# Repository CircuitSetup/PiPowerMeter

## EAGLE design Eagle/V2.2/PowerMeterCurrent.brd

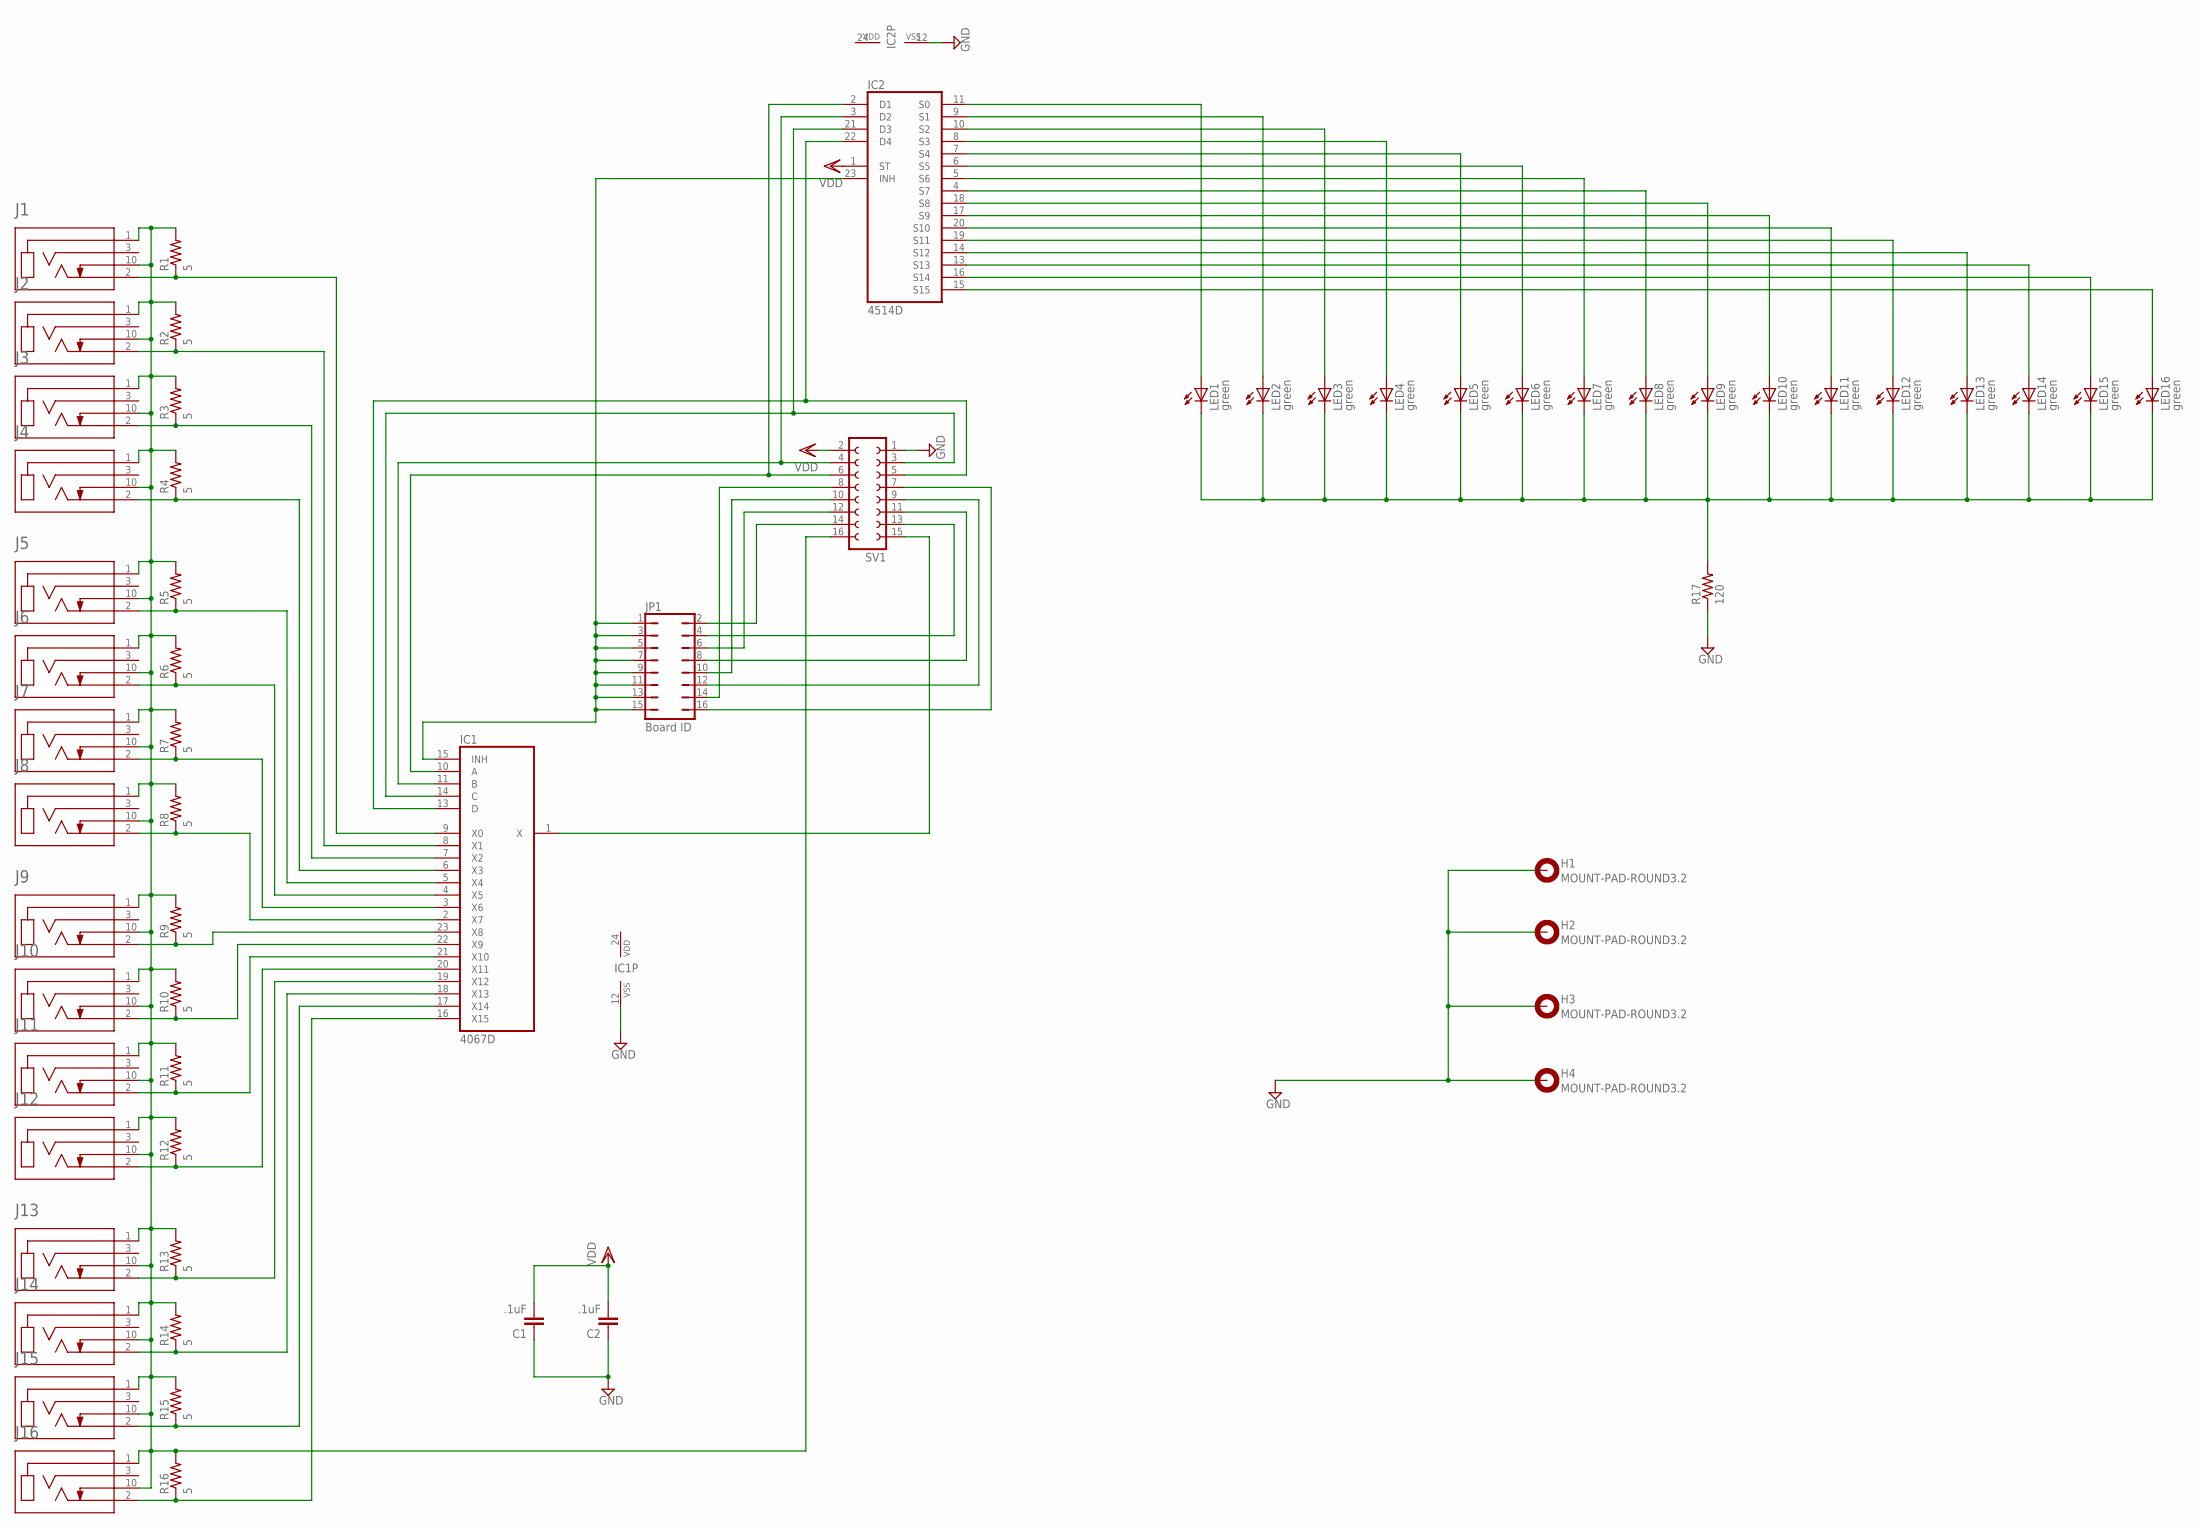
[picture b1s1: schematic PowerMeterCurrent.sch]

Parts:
C1, C2: .1uF; C1206; PARTNO C1206C104K5RAC7867
H1, H2, H3, H4: MOUNT-PAD-ROUND3.2; 3,2-PAD
IC1: 4067D; SO24W; PARTNO 74HC4067D,652
IC2: 4514D; SO24W; PARTNO 74HC4514D,652
J1, J2, J3, J4, J5, J6, J7, J8, J9, J10, J11, J12, J13, J14, J15, J16: SJ2-35813B-SMT-TR; CUI_SJ2-35813B-SMT-TR
JP1: Board ID; JP8Q; PARTNO 67996-416HLF
LED1, LED2, LED3, LED4, LED5, LED6, LED7, LED8, LED9, LED10, LED11, LED12, LED13, LED14, LED15, LED16: green; LED_1206; PARTNO LTST-C150GKT
R1, R2, R3, R4, R5, R6, R7, R8, R9, R10, R11, R12, R13, R14, R15, R16: 5; R1206; PARTNO RC1206FR-075R1L
R17: 120; R1206; PARTNO RC1206FR-07120RL
SV1: FE08-2; PARTNO SSQ-108-02-T-D

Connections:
CT-: J1.1 (SLEEVE), J1.10 (TIP_SWITCH), J2.1 (SLEEVE), J2.10 (TIP_SWITCH), J3.1 (SLEEVE), J3.10 (TIP_SWITCH), J4.1 (SLEEVE), J4.10 (TIP_SWITCH), J5.1 (SLEEVE), J5.10 (TIP_SWITCH), J6.1 (SLEEVE), J6.10 (TIP_SWITCH), J7.1 (SLEEVE), J7.10 (TIP_SWITCH), J8.1 (SLEEVE), J8.10 (TIP_SWITCH), J9.1 (SLEEVE), J9.10 (TIP_SWITCH), J10.1 (SLEEVE), J10.10 (TIP_SWITCH), J11.1 (SLEEVE), J11.10 (TIP_SWITCH), J12.1 (SLEEVE), J12.10 (TIP_SWITCH), J13.1 (SLEEVE), J13.10 (TIP_SWITCH), J14.1 (SLEEVE), J14.10 (TIP_SWITCH), J15.1 (SLEEVE), J15.10 (TIP_SWITCH), J16.1 (SLEEVE), J16.10 (TIP_SWITCH), R1.2, R2.2, R3.2, R4.2, R5.2, R6.2, R7.2, R8.2, R9.2, R10.2, R11.2, R12.2, R13.2, R14.2, R15.2, R16.2, SV1.16
GND: C1.1, C2.1, H1.B3,2, H2.B3,2, H3.B3,2, H4.B3,2, IC1.12 (VSS), IC2.12 (VSS), R17.1, SV1.1
unnamed: IC1.10 (A), IC2.2 (D1), SV1.6
unnamed: IC2.15 (S15), LED16.A
unnamed: IC1.11 (B), IC2.3 (D2), SV1.4
unnamed: IC1.14 (C), IC2.21 (D3), SV1.3
unnamed: IC1.13 (D), IC2.22 (D4), SV1.5
unnamed: IC1.15 (INH), IC2.23 (INH), JP1.1, JP1.3, JP1.5, JP1.7, JP1.9, JP1.11, JP1.13, JP1.15
unnamed: JP1.14, SV1.8
unnamed: JP1.10, SV1.10
unnamed: IC2.16 (S14), LED15.A
unnamed: JP1.6, SV1.12
unnamed: JP1.2, SV1.14
unnamed: JP1.4, SV1.13
unnamed: JP1.8, SV1.11
unnamed: JP1.12, SV1.9
unnamed: JP1.16, SV1.7
unnamed: IC1.1 (X), SV1.15
unnamed: IC1.5 (X4), J5.2 (TIP), R5.1
unnamed: IC2.13 (S13), LED14.A
unnamed: IC1.9 (X0), J1.2 (TIP), R1.1
unnamed: LED1.C, LED2.C, LED3.C, LED4.C, LED5.C, LED6.C, LED7.C, LED8.C, LED9.C, LED10.C, LED11.C, LED12.C, LED13.C, LED14.C, LED15.C, LED16.C, R17.2
unnamed: IC1.8 (X1), J2.2 (TIP), R2.1
unnamed: IC1.7 (X2), J3.2 (TIP), R3.1
unnamed: IC1.6 (X3), J4.2 (TIP), R4.1
unnamed: IC1.4 (X5), J6.2 (TIP), R6.1
unnamed: IC1.3 (X6), J7.2 (TIP), R7.1
unnamed: IC1.2 (X7), J8.2 (TIP), R8.1
unnamed: IC1.23 (X8), J9.2 (TIP), R9.1
unnamed: IC2.14 (S12), LED13.A
unnamed: IC2.19 (S11), LED12.A
unnamed: IC2.20 (S10), LED11.A
unnamed: IC2.17 (S9), LED10.A
unnamed: IC2.18 (S8), LED9.A
unnamed: IC2.4 (S7), LED8.A
unnamed: IC2.5 (S6), LED7.A
unnamed: IC2.6 (S5), LED6.A
unnamed: IC2.7 (S4), LED5.A
unnamed: IC2.8 (S3), LED4.A
unnamed: IC1.22 (X9), J10.2 (TIP), R10.1
unnamed: IC1.21 (X10), J11.2 (TIP), R11.1
unnamed: IC2.10 (S2), LED3.A
unnamed: IC2.9 (S1), LED2.A
unnamed: IC2.11 (S0), LED1.A
unnamed: IC1.20 (X11), J12.2 (TIP), R12.1
unnamed: IC1.18 (X13), J14.2 (TIP), R14.1
unnamed: IC1.17 (X14), J15.2 (TIP), R15.1
unnamed: IC1.19 (X12), J13.2 (TIP), R13.1
unnamed: IC1.16 (X15), J16.2 (TIP), R16.1
VDD: C1.2, C2.2, IC1.24 (VDD), IC2.1 (ST), IC2.24 (VDD), SV1.2

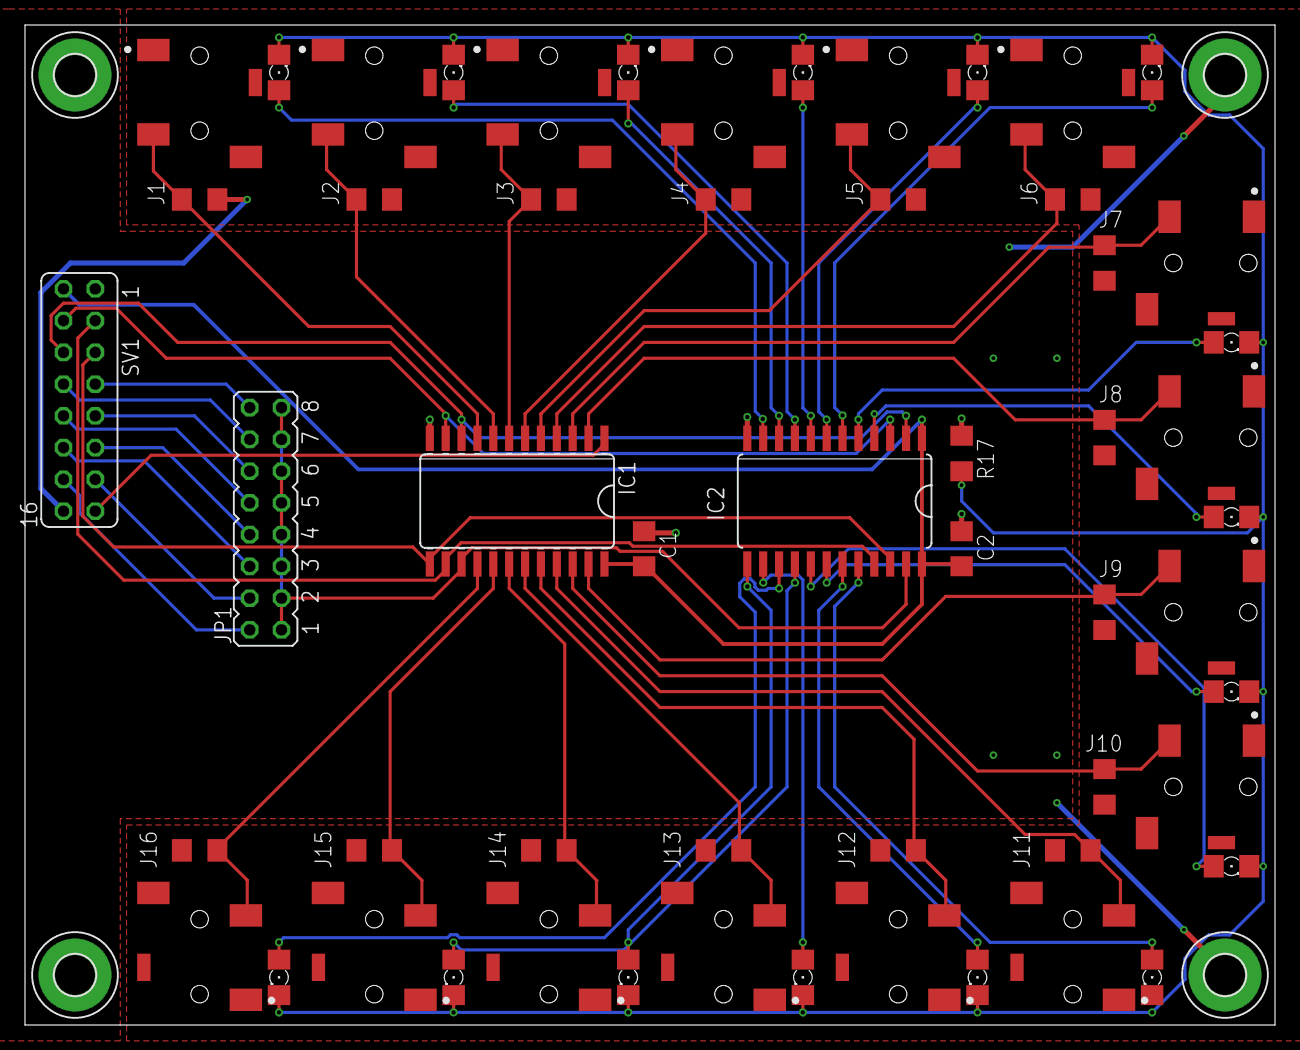
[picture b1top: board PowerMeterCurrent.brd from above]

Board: 2 copper layers, 100.0 x 80.0 mm, 59 parts (0 on the bottom side), 50 nets.

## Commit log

2019-03-02 Cleaned up some thing
    cleaned up traces, made 3.5mm connectors, caps & diode SMD, put everything on same side of boards (may need to put resistor arrays back on the underside of the main board).
2019-03-03 fixed some silk screen labels & added pics
